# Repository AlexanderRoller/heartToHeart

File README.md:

# HeartToHeart

HeartToHeart is a hardware project designed for IoT prototyping, featuring a custom PCB and ESP32 microcontroller. The project includes AWS IoT integration, a custom display, and a complete KiCad design for fabrication and assembly.

## Features
- Custom PCB design (KiCad)
- ESP32 microcontroller
- AWS IoT Core connectivity
- OLED display (NHD-C12832A1Z-FSW-FBW-3V3)
- Example firmware for secure WiFi and AWS IoT connection

## Directory Structure
- `pcb/` – KiCad project files and backups
- `src/` – Firmware source code and secrets templates
- `pcb/media/` – Project images and schematic PDF

## Getting Started
1. **Clone the repository**
2. Copy `src/secrets.example.h` to `src/secrets.h` and fill in your WiFi and AWS IoT credentials
3. Open `pcb/pcb.kicad_pro` in KiCad to view or modify the PCB
4. Generate your own fabrication files (Gerbers, drills, etc.) using KiCad's plot and export tools
5. Flash the firmware in `src/src.ino` to your ESP32

## Images

### PCB Layout

### Schematic

## License
See `pcb/License.txt` for licensing information.

---

**Note:** Do not commit your real `src/secrets.h` with credentials. Use `src/secrets.example.h` as a template.

**Important:** Fabrication files (Gerbers, drills, etc.) are not included in the repository. You must generate your own using the provided KiCad project files.

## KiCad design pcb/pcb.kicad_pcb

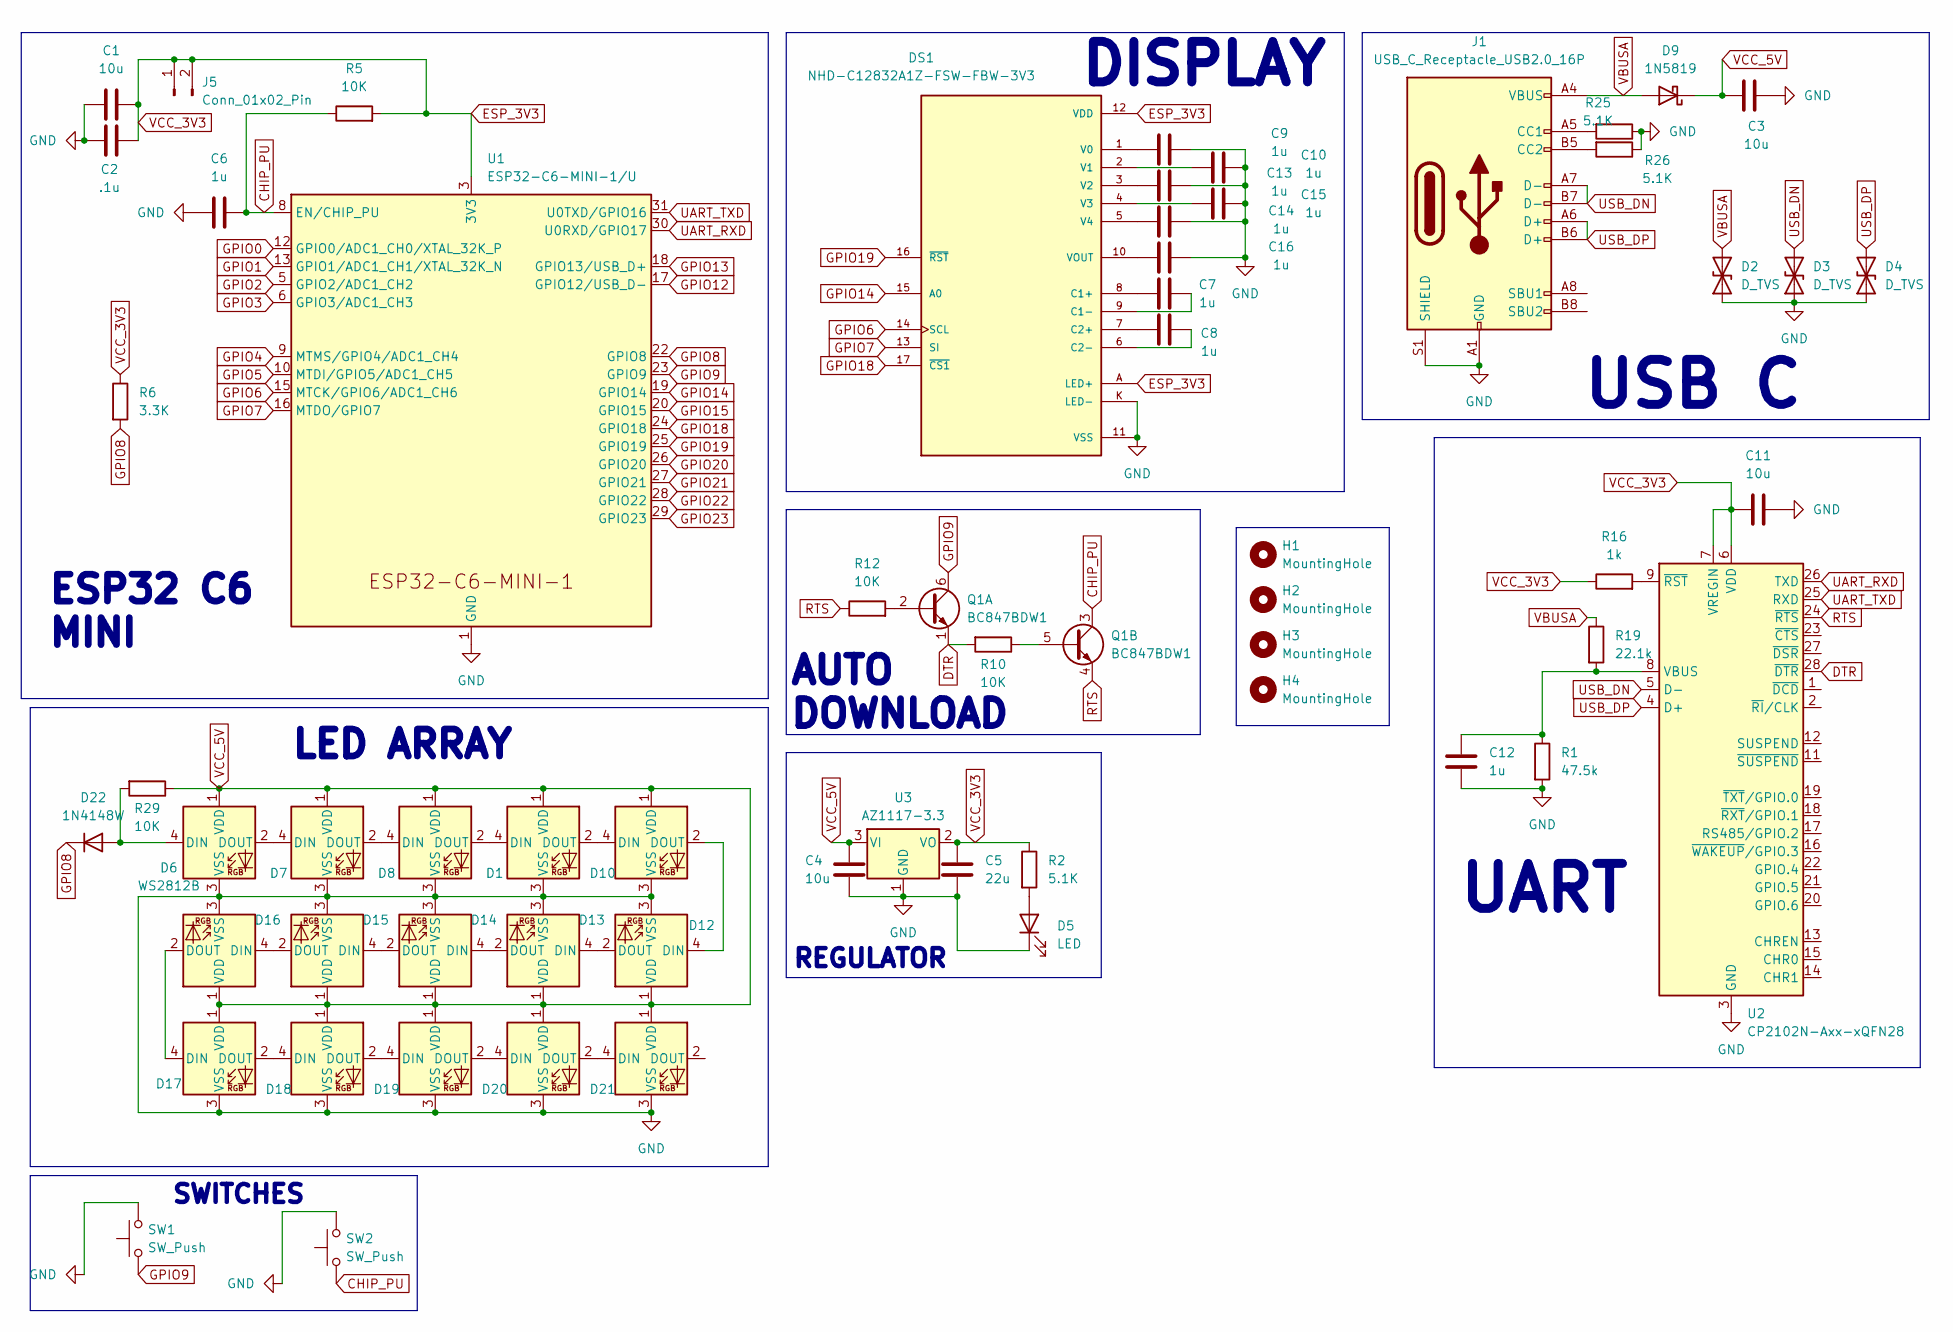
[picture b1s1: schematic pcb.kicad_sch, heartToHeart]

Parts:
C1, C3, C4, C11: 10u; C_0805_2012Metric_Pad1.18x1.45mm_HandSolder
C2: .1u; C_0805_2012Metric_Pad1.18x1.45mm_HandSolder
C5: 22u; C_0805_2012Metric_Pad1.18x1.45mm_HandSolder
C6, C7, C8, C9, C10, C12, C13, C14, C15, C16: 1u; C_0805_2012Metric_Pad1.18x1.45mm_HandSolder
D1, D6, D7, D8, D10, D12, D13, D14, D15, D16, D17, D18, D19, D20, D21: WS2812B; LED_WS2812B_PLCC4_5.0x5.0mm_P3.2mm
D2, D3, D4: D_TVS; D_SOD-523
D5: LED; LED_0805_2012Metric_Pad1.15x1.40mm_HandSolder
D9: 1N5819; D_SOD-123
D22: 1N4148W; D_SOD-123
DS1: NHD-C12832A1Z-FSW-FBW-3V3; NHD-C12832A1Z-FSRGB; PARTREV 7; DigiKey_Part_Number NHD-C12832A1Z-FSW-FBW-3V3-ND
H1, H2, H3, H4: MountingHole; MountingHole_2.5mm
J1: USB_C_Receptacle_USB2.0_16P; USB_C_Receptacle_GCT_USB4105-xx-A_16P_TopMnt_Horizontal
J5: Conn_01x02_Pin; PinHeader_1x02_P2.54mm_Vertical
Q1: BC847BDW1; SOT-363_SC-70-6_Handsoldering
R1: 47.5k; R_0805_2012Metric_Pad1.20x1.40mm_HandSolder
R2, R25, R26: 5.1K; R_0805_2012Metric_Pad1.20x1.40mm_HandSolder
R5, R10, R12, R29: 10K; R_0805_2012Metric_Pad1.20x1.40mm_HandSolder
R6: 3.3K; R_0805_2012Metric_Pad1.20x1.40mm_HandSolder
R16: 1k; R_0805_2012Metric_Pad1.20x1.40mm_HandSolder
R19: 22.1k; R_0805_2012Metric_Pad1.20x1.40mm_HandSolder
SW1, SW2: SW_Push; SW_SPST_PTS647_Sx38
U1: ESP32-C6-MINI-1/U; ESP32-C6-MINI-1
U2: CP2102N-Axx-xQFN28; QFN-28-1EP_5x5mm_P0.5mm_EP3.25x3.25mm
U3: AZ1117-3.3; SOT-223-3_TabPin2

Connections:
CHIP_PU: C6.2, Q1.3 (C2), R5.1, SW2.1, U1.8 (EN/CHIP_PU)
DTR: Q1.1 (E1), R10.2, U2.28 (~DTR)
ESP_3V3: C1.2, C2.2, C5.1, C11.1, DS1.12 (VDD), DS1.A (LED+), J5.1, J5.2, R2.1, R5.2, R6.1, R16.1, U1.3 (3V3), U2.6 (VDD), U2.7 (VREGIN), U3.2 (VO)
GND: C1.1, C2.1, C3.2, C4.2, C5.2, C6.1, C9.2, C10.2, C11.2, C12.1, C13.2, C14.2, C15.2, C16.2, D1.3 (VSS), D2.1 (A1), D3.1 (A1), D4.1 (A1), D5.1 (K), D6.3 (VSS), D7.3 (VSS), D8.3 (VSS), D10.3 (VSS), D12.3 (VSS), D13.3 (VSS), D14.3 (VSS), D15.3 (VSS), D16.3 (VSS), D17.3 (VSS), D18.3 (VSS), D19.3 (VSS), D20.3 (VSS), D21.3 (VSS), DS1.11 (VSS), DS1.K (LED-), J1.A1 (GND), J1.A12 (GND), J1.B1 (GND), J1.B12 (GND), J1.S1 (SHIELD), R1.2, R25.1, R26.1, SW1.2, SW2.2, U1.1 (GND), U1.2 (GND), U1.11 (GND), U1.14 (GND), U1.36 (GND), U1.37 (GND), U1.38 (GND), U1.39 (GND), U1.40 (GND), U1.41 (GND), U1.42 (GND), U1.43 (GND), U1.44 (GND), U1.45 (GND), U1.46 (GND), U1.47 (GND), U1.48 (GND), U1.49 (GND), U1.50 (GND), U1.51 (GND), U1.52 (GND), U1.53 (GND), U2.3 (GND), U2.29 (GND), U3.1 (GND)
GPIO0: U1.12 (GPIO0/ADC1_CH0/XTAL_32K_P)
GPIO1: U1.13 (GPIO1/ADC1_CH1/XTAL_32K_N)
GPIO2: U1.5 (GPIO2/ADC1_CH2)
GPIO3: U1.6 (GPIO3/ADC1_CH3)
GPIO4: U1.9 (MTMS/GPIO4/ADC1_CH4)
GPIO5: U1.10 (MTDI/GPIO5/ADC1_CH5)
GPIO6: DS1.14 (SCL), U1.15 (MTCK/GPIO6/ADC1_CH6)
GPIO7: DS1.13 (SI), U1.16 (MTDO/GPIO7)
GPIO8: D22.1 (K), R6.2, U1.22 (GPIO8)
GPIO9: Q1.6 (C1), SW1.1, U1.23 (GPIO9)
GPIO12: U1.17 (GPIO12/USB_D-)
GPIO13: U1.18 (GPIO13/USB_D+)
GPIO14: DS1.15 (A0), U1.19 (GPIO14)
GPIO15: U1.20 (GPIO15)
GPIO18: DS1.17 (~CS1), U1.24 (GPIO18)
GPIO19: DS1.16 (~RST), U1.25 (GPIO19)
GPIO20: U1.26 (GPIO20)
GPIO21: U1.27 (GPIO21)
GPIO22: U1.28 (GPIO22)
GPIO23: U1.29 (GPIO23)
unnamed: D1.4 (DIN), D8.2 (DOUT)
unnamed: D1.2 (DOUT), D10.4 (DIN)
unnamed: D5.2 (A), R2.2
unnamed: D6.2 (DOUT), D7.4 (DIN)
unnamed: D7.2 (DOUT), D8.4 (DIN)
unnamed: D10.2 (DOUT), D12.4 (DIN)
unnamed: D12.2 (DOUT), D13.4 (DIN)
unnamed: D13.2 (DOUT), D14.4 (DIN)
unnamed: D14.2 (DOUT), D15.4 (DIN)
unnamed: D15.2 (DOUT), D16.4 (DIN)
unnamed: D16.2 (DOUT), D17.4 (DIN)
unnamed: D17.2 (DOUT), D18.4 (DIN)
unnamed: D18.2 (DOUT), D19.4 (DIN)
unnamed: D19.2 (DOUT), D20.4 (DIN)
unnamed: D20.2 (DOUT), D21.4 (DIN)
unnamed: D6.4 (DIN), D22.2 (A), R29.2
unnamed: C7.1, DS1.8 (C1+)
unnamed: C7.2, DS1.9 (C1-)
unnamed: C8.1, DS1.7 (C2+)
unnamed: C8.2, DS1.6 (C2-)
unnamed: C9.1, DS1.1 (V0)
unnamed: C10.1, DS1.2 (V1)
unnamed: C13.1, DS1.3 (V2)
unnamed: C15.1, DS1.4 (V3)
unnamed: C14.1, DS1.5 (V4)
unnamed: C16.1, DS1.10 (VOUT)
unnamed: J1.A5 (CC1), R25.2
unnamed: J1.B5 (CC2), R26.2
unnamed: Q1.2 (B1), R12.2
unnamed: Q1.5 (B2), R10.1
unnamed: C12.2, R1.1, R19.2, U2.8 (VBUS)
unnamed: R16.2, U2.9 (~RST)
RTS: Q1.4 (E2), R12.1, U2.24 (~RTS)
UART_RXD: U1.30 (U0RXD/GPIO17), U2.26 (TXD)
UART_TXD: U1.31 (U0TXD/GPIO16), U2.25 (RXD)
USB_DN: D3.2 (A2), J1.A7 (D-), J1.B7 (D-), U2.5 (D-)
USB_DP: D4.2 (A2), J1.A6 (D+), J1.B6 (D+), U2.4 (D+)
VBUSA: D2.2 (A2), D9.2 (A), J1.A4 (VBUS), J1.A9 (VBUS), J1.B4 (VBUS), J1.B9 (VBUS), R19.1
VCC_5V: C3.1, C4.1, D1.1 (VDD), D6.1 (VDD), D7.1 (VDD), D8.1 (VDD), D9.1 (K), D10.1 (VDD), D12.1 (VDD), D13.1 (VDD), D14.1 (VDD), D15.1 (VDD), D16.1 (VDD), D17.1 (VDD), D18.1 (VDD), D19.1 (VDD), D20.1 (VDD), D21.1 (VDD), R29.1, U3.3 (VI)

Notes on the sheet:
LED ARRAY
ESP32 C6 MINI
UART
REGULATOR
SWITCHES
DISPLAY
AUTO DOWNLOAD
USB C

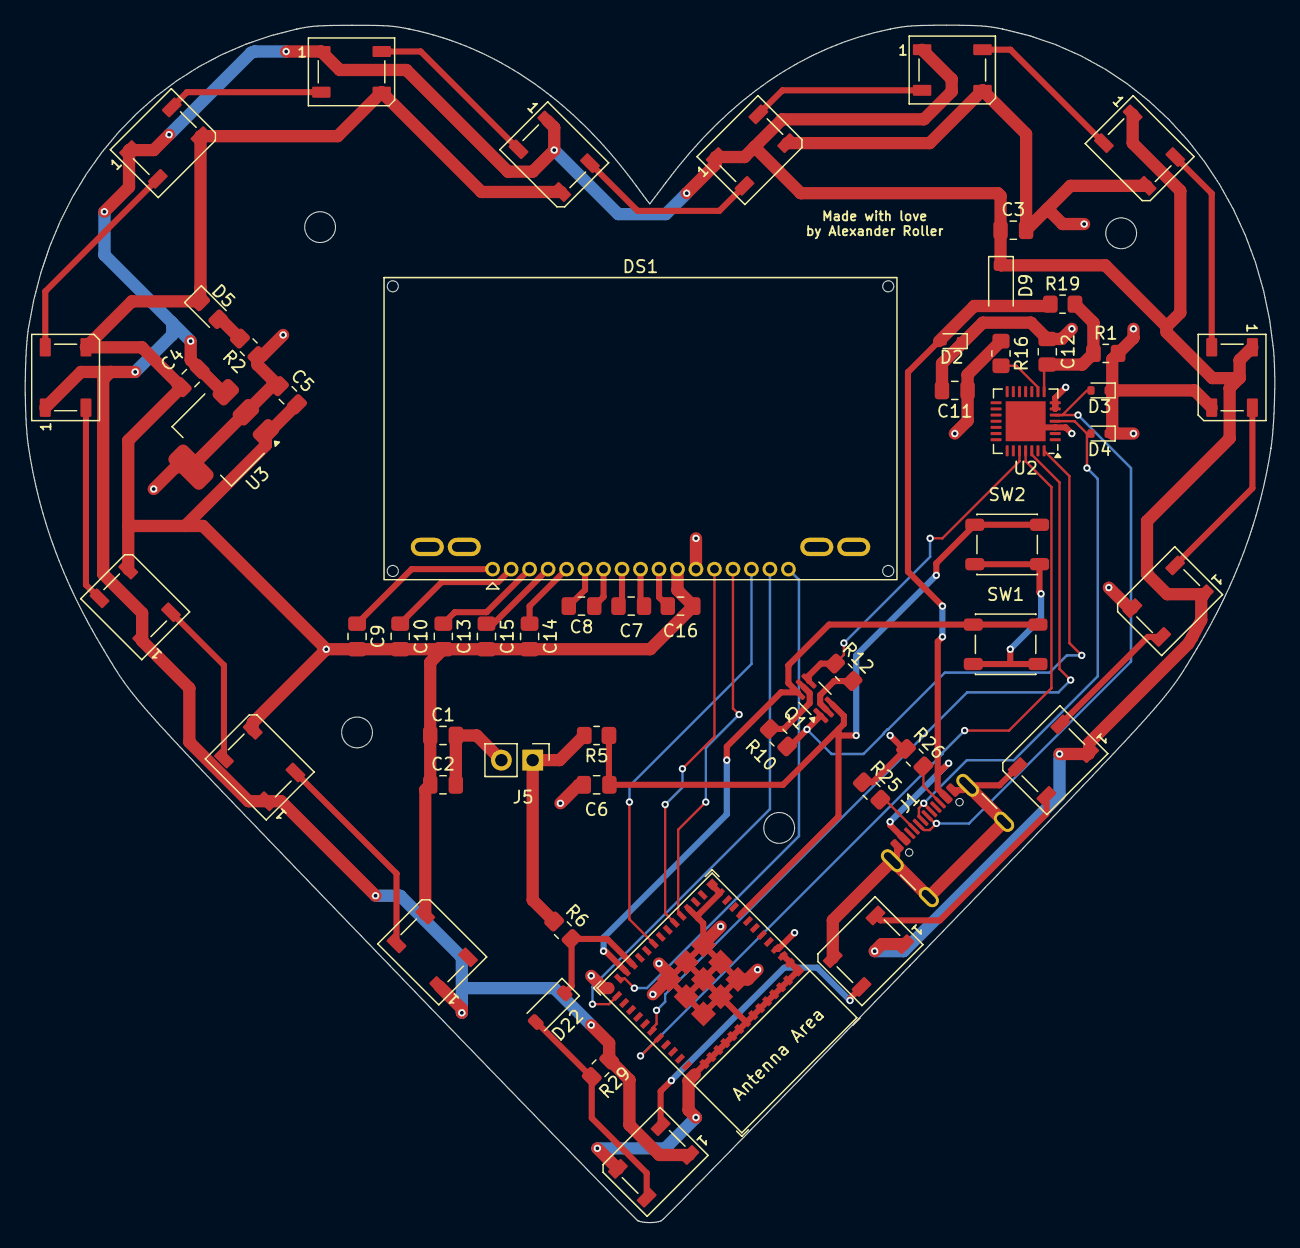
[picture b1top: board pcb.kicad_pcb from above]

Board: 4 copper layers, 101.4 x 97.2 mm, 61 parts (0 on the bottom side), 50 nets.

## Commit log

2025-06-04 add pcb photo
2025-06-04 readme and secrets example
